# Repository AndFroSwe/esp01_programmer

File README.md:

# esp01_programmer
Programming board for the ESP01 (ESP8266)

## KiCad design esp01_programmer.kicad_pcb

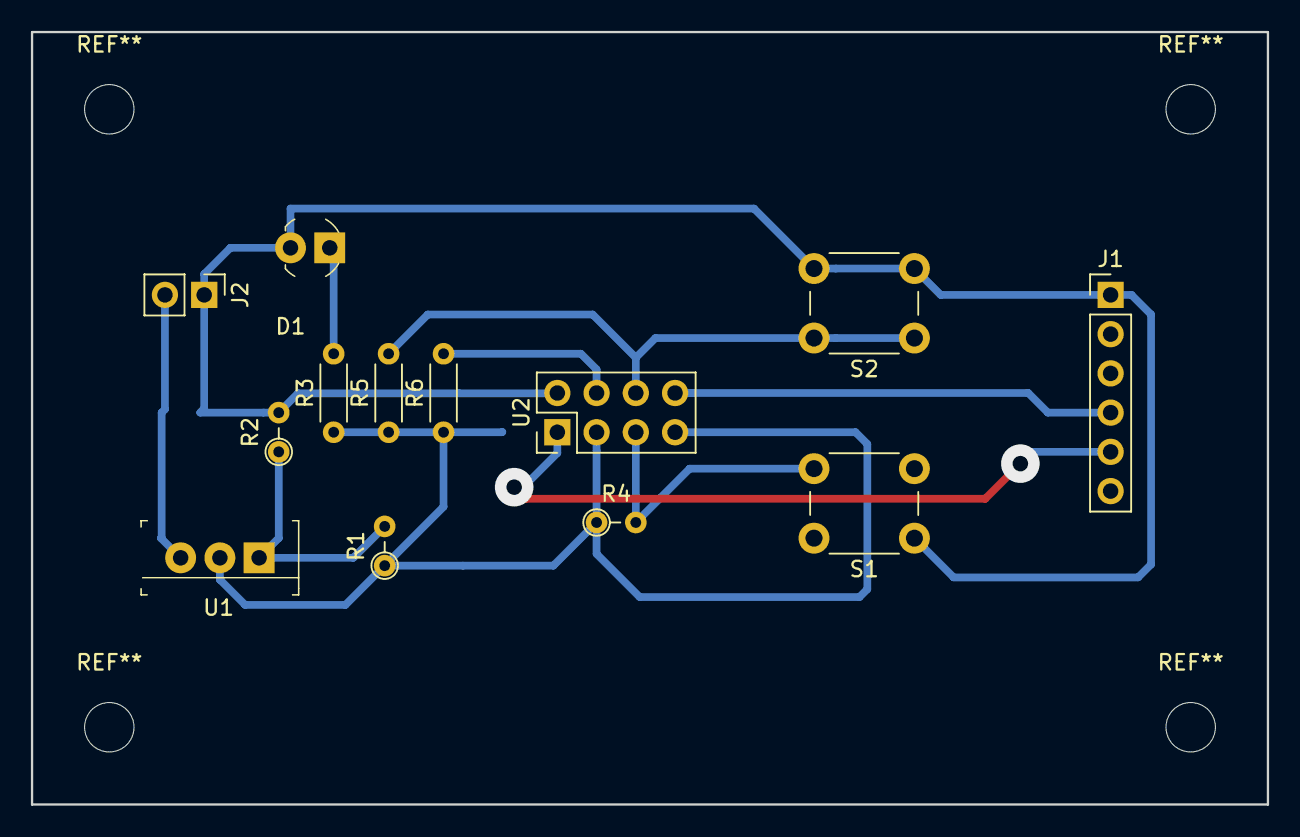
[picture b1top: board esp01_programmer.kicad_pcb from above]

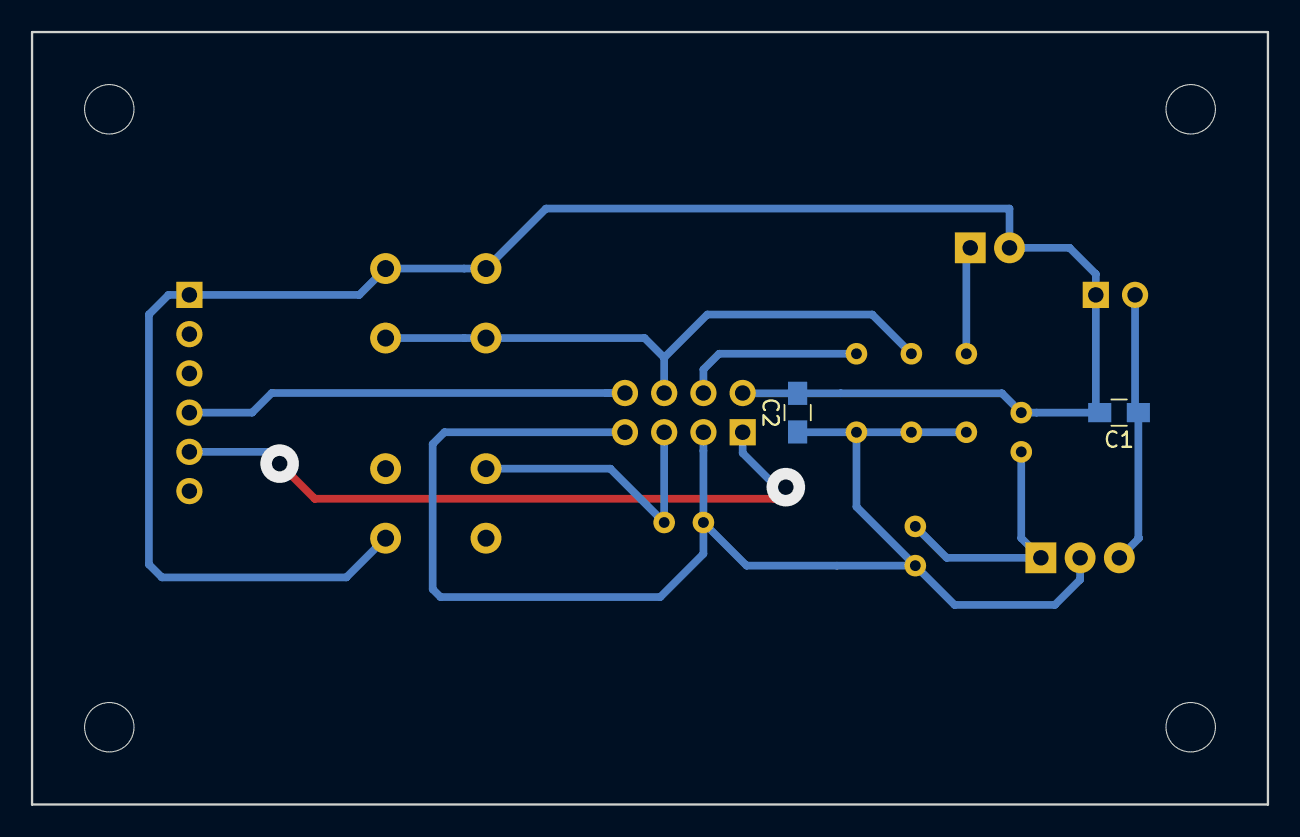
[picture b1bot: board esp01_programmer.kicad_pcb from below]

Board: 2 copper layers, 80.0 x 50.0 mm, 15 parts (2 on the bottom side), 10 nets.

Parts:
C1: 0.1 uF; C_0805_HandSoldering
C2: 220uF; C_0805_HandSoldering
D1: 151033RS03000; LED_3mm_Radial
J1: Conn_01x06_Female; Pin_Header_Straight_1x06_Pitch2.54mm
J2: Conn_01x02_Female; Pin_Header_Straight_1x02_Pitch2.54mm
R1: 240; R_Axial_DIN0204_L3.6mm_D1.6mm_P2.54mm_Vertical
R2: 400; R_Axial_DIN0204_L3.6mm_D1.6mm_P2.54mm_Vertical
R3: 60; R_Axial_DIN0204_L3.6mm_D1.6mm_P5.08mm_Horizontal
R4: 10k; R_Axial_DIN0204_L3.6mm_D1.6mm_P2.54mm_Vertical
R5, R6: 10k; R_Axial_DIN0204_L3.6mm_D1.6mm_P5.08mm_Horizontal
S1, S2: GPTS203211B; SW_PUSH_6mm_h4.3mm
U1: LM317T; TO-220-3
U2: ESP-01v090; Pin_Header_Straight_2x04_Pitch2.54mm

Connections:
+3V3: C2.1, R1.1, R3.1, R4.1, R5.1, R6.1, U1.2, U2.3, U2.7
/FTDI_RX: J1.5, U2.1
/FTDI_TX: J1.4, U2.8
GND: C1.2, C2.2, D1.2, J1.1, J2.1, R2.2, S1.1, S2.2, U2.2
unnamed: D1.1, R3.2
unnamed: R1.2, R2.1, U1.1
unnamed: R4.2, S1.2, U2.5
unnamed: R5.2, S2.1, U2.6
unnamed: R6.2, U2.4
VCC: C1.1, J2.2, U1.3

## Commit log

2018-09-30 Initial commit, have pcb and case
2018-09-30 Made export edits to case
